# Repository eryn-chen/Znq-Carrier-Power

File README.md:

# Zynq-Carrier-Template
A template Daughterboard for pinguz97's Zynq-SoM

## Reference Documents
https://github.com/pinguz97/Zynq-SoM/

## Contains
- KiCAD Schematic
- KiCAD Footprint
- 3D Models
- Example Project

## Usage of KiCAD Symbol and Footprint
- Copy the `imports` folder of this repository into the top folder of your KiCAD Project
- Select the appropriate files in KiCAD under Tools -> Manage Symbol/Footrpint Library

## Images
### 3D Model

### Schematic

### PCB

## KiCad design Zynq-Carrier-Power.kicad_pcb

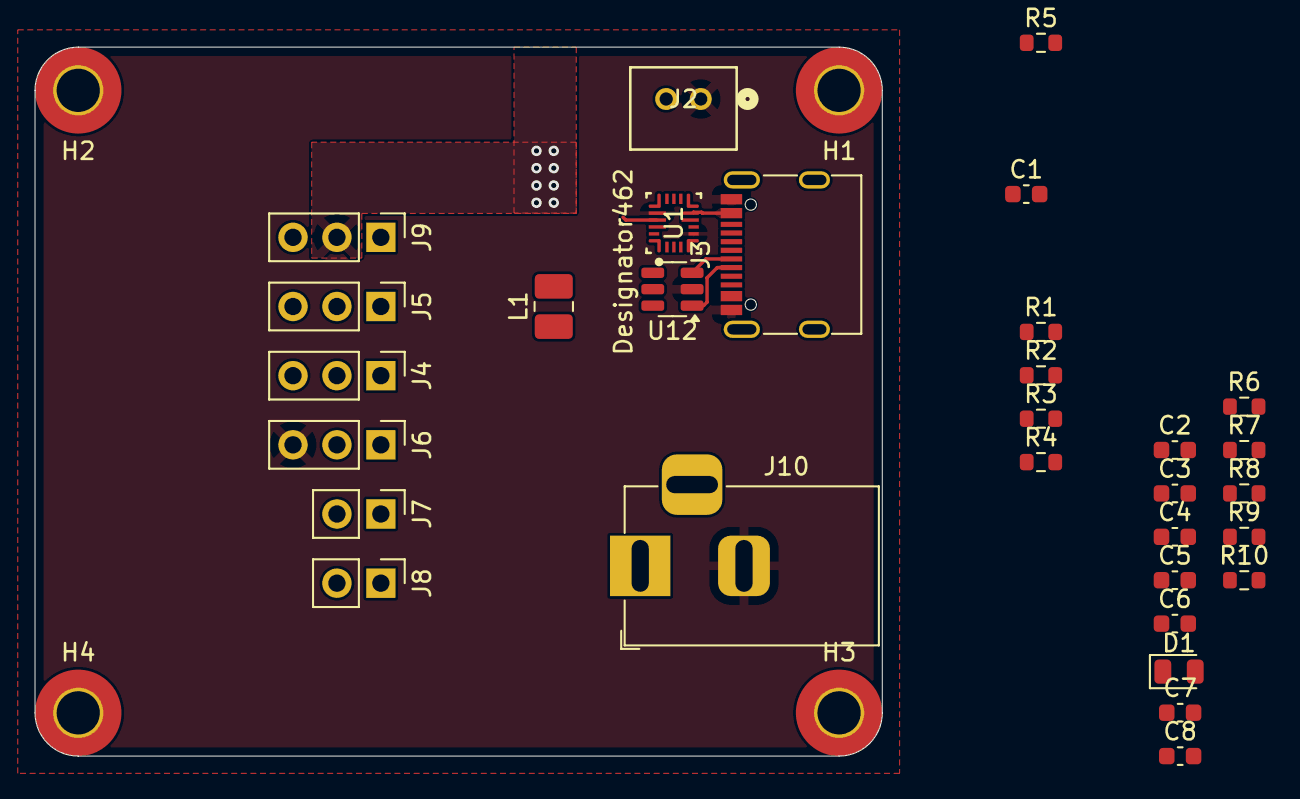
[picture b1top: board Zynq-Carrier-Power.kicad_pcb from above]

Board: 2 copper layers, 49.0 x 41.0 mm, 36 parts (1 on the bottom side), 28 nets.

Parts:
C1, C3, C5: 10uf; C_0603_1608Metric
C2, C4, C6: 0.1uf; C_0603_1608Metric
C7: 4.7 uF; C_0603_1608Metric
C8: 47 nF; C_0603_1608Metric
D1: LED; LED_0805_2012Metric
H1, H2, H3, H4: MountingHole_Pad; MountingHole_2.5mm_Pad_TopBottom
J1: Zynq_SoM
J2: B2B-PH-K-S; CONN2_B2B-PH-K-S_JST
J3: USB_C_Receptacle_USB2.0_16P; USB_C_Receptacle_G-Switch_GT-USB-7010ASV
J4, J5, J6, J9: Conn_01x03; PinHeader_1x03_P2.54mm_Vertical
J7, J8: Conn_01x02; PinHeader_1x02_P2.54mm_Vertical
J10: Barrel_Jack_MountingPin; BarrelJack_Horizontal
L1: L; L_1008_2520Metric_Pad1.43x2.20mm_HandSolder
R1, R2, R3: 5.1k; R_0603_1608Metric
R4: 1M; R_0603_1608Metric
R5: 100k; R_0603_1608Metric
R6: 330; R_0603_1608Metric
R7, R10: 10K; R_0603_1608Metric
R8, R9: 4.7k; R_0603_1608Metric
U1: BQ25629RYKR; RYK0018A-MFG
U12: SRV05-4; SOT-23-6

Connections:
+5V: J1.1 (VIN), J1.2 (VIN), J1.3 (VIN), J1.4 (VIN), J1.5 (VIN), J1.6 (VIN), J1.7 (VIN), J1.8 (VIN), J1.9 (VIN), J1.10 (VIN), J1.11 (VIN), J1.12 (VIN), J1.13 (VIN), J1.14 (VIN), J9.2, R8.1, R9.1
/SCL: J7.2, R7.1, U1.13 (SCL)
/SDA: J8.2, R10.1, U1.12 (SDA)
/USB_D+: J3.A6 (D+), J3.B6 (D+), J5.2, U12.3 (IO2)
/USB_D-: J3.A7 (D-), J3.B7 (D-), J4.2, U12.1 (IO1)
/USB_POW_D+: J5.1, U1.5 (D+)
/USB_POW_D-: J4.1, U1.4 (D-)
/USB_SOM_D+: J1.32 (USB_D+), J5.3
/USB_SOM_D-: J1.30 (USB_D-), J4.3
GND: C1.2, C2.2, C3.2, C4.2, C5.2, C6.2, C7.2, D1.1 (K), J1.15 (GND), J1.16 (GND), J1.17 (GND), J1.18 (GND), J1.23 (GND), J1.28 (GND), J1.39 (GND), J1.44 (GND), J1.51 (GND), J1.62 (GND), J1.63 (GND), J1.72 (GND), J1.75 (GND), J1.81 (GND), J1.82 (GND), J1.87 (GND), J1.96 (GND), J1.99 (GND), J1.104 (GND), J1.105 (GND), J1.106 (GND), J1.115 (GND), J1.116 (GND), J1.125 (GND), J1.126 (GND), J1.135 (GND), J1.136 (GND), J1.145 (GND), J1.146 (GND), J1.155 (GND), J1.165 (GND), J1.166 (GND), J1.175 (GND), J1.176 (GND), J1.185 (GND), J1.186 (GND), J1.195 (GND), J1.196 (GND), J1.197 (GND), J1.203 (GND), J1.206 (GND), J1.213 (GND), J1.218 (GND), J1.223 (GND), J1.228 (GND), J1.233 (GND), J1.238 (GND), J1.243 (GND), J1.248 (GND), J1.253 (GND), J1.258 (GND), J1.263 (GND), J1.268 (GND), J1.273 (GND), J1.280 (GND), J1.283 (GND), J1.290 (GND), J1.295 (GND), J1.300 (GND), J2.1, J3.A1 (GND), J3.A12 (GND), J3.B1 (GND), J3.B12 (GND), J6.3, J10.2, R1.1, R2.1, R4.2, R5.2, U1.6 (TS), U1.15 (GND), U12.2 (VN)
unnamed: D1.2 (A), R6.2
unnamed: J3.A5 (CC1), R1.2
unnamed: J3.B5 (CC2), R2.2
unnamed: J3.S1 (SHIELD), R4.1
unnamed: J6.1, R7.2
unnamed: J6.2, R10.2
unnamed: J7.1, R8.2
unnamed: J8.1, R9.2
unnamed: C8.2, U1.1 (BTST)
unnamed: C1.1, C2.1, U1.17 (PMID)
unnamed: C7.1, U1.2 (REGN)
unnamed: R6.1, U1.10 (STAT)
unnamed: C8.1, L1.1, U1.16 (SW)
unnamed: R3.2, U12.5 (VP)
VBAT: J2.2, U1.8 (BAT)
VREG_OUT: J9.1, L1.2, U1.9 (SYS)
V_USB: C3.1, C4.1, C5.1, C6.1, J3.A4 (VBUS), J3.A9 (VBUS), J3.B4 (VBUS), J3.B9 (VBUS), R3.1, R5.1, U1.18 (VBUS)
Vps: J9.3, J10.1

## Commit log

2025-06-23 Renamed and Updated Silkscreen
2025-08-14 Squashed commit of the following:
    commit 0ad81e69922d32d90721302da68770b5998e2075
    Author: pixelatedknight27 <97324570+pixelatedknight27@users.noreply.github.com>
    Date: Wed Aug 6 21:23:02 2025 -0700
    Updated Schematic Switching Regulator Output
    commit 8c5282f5a799869a6680777a751af97c305c1966
    Author: pixelatedknight27 <maxgross72@gmail.com>
2025-08-14 Project Rename
2025-08-14 moved cap
2025-08-14 Unmoved cap
